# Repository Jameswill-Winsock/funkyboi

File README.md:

# funkyboi
a funky chonky handheld gba clone

he's a work in progress, please bear with him

## What is this?
like you read, a gba clone. its meant to be as small in form factor as possible, and currently i've nearly achieved this. 
it borrows from the solderparty stamp xl in form of the schematic, but pcb was remade because it wouldn't open for me for some reason. some differences between those and this are:
- lack of castelled edge based breakout (swapped to normal through holes)
- no proper power plane or signal plane (i have no idea how those work, i only know ground copper pour)
- power network significantly changed to be more unified (arguably, more unstable, but throw on some 100nf capacitors and it fixes everything.)
- the obvious gamer setup

## Parts used
please refer to "BOM reference.csv". Has everything for now,

## Journal.md
included please check

## Photos

yes i know the elephant in the room is the big red cross marks
they're marked do not populate because i want to leave the headers alone until i need them and for the actual parts that'll be needed i'll hand solder what i can

## Thanks
to you for coming here

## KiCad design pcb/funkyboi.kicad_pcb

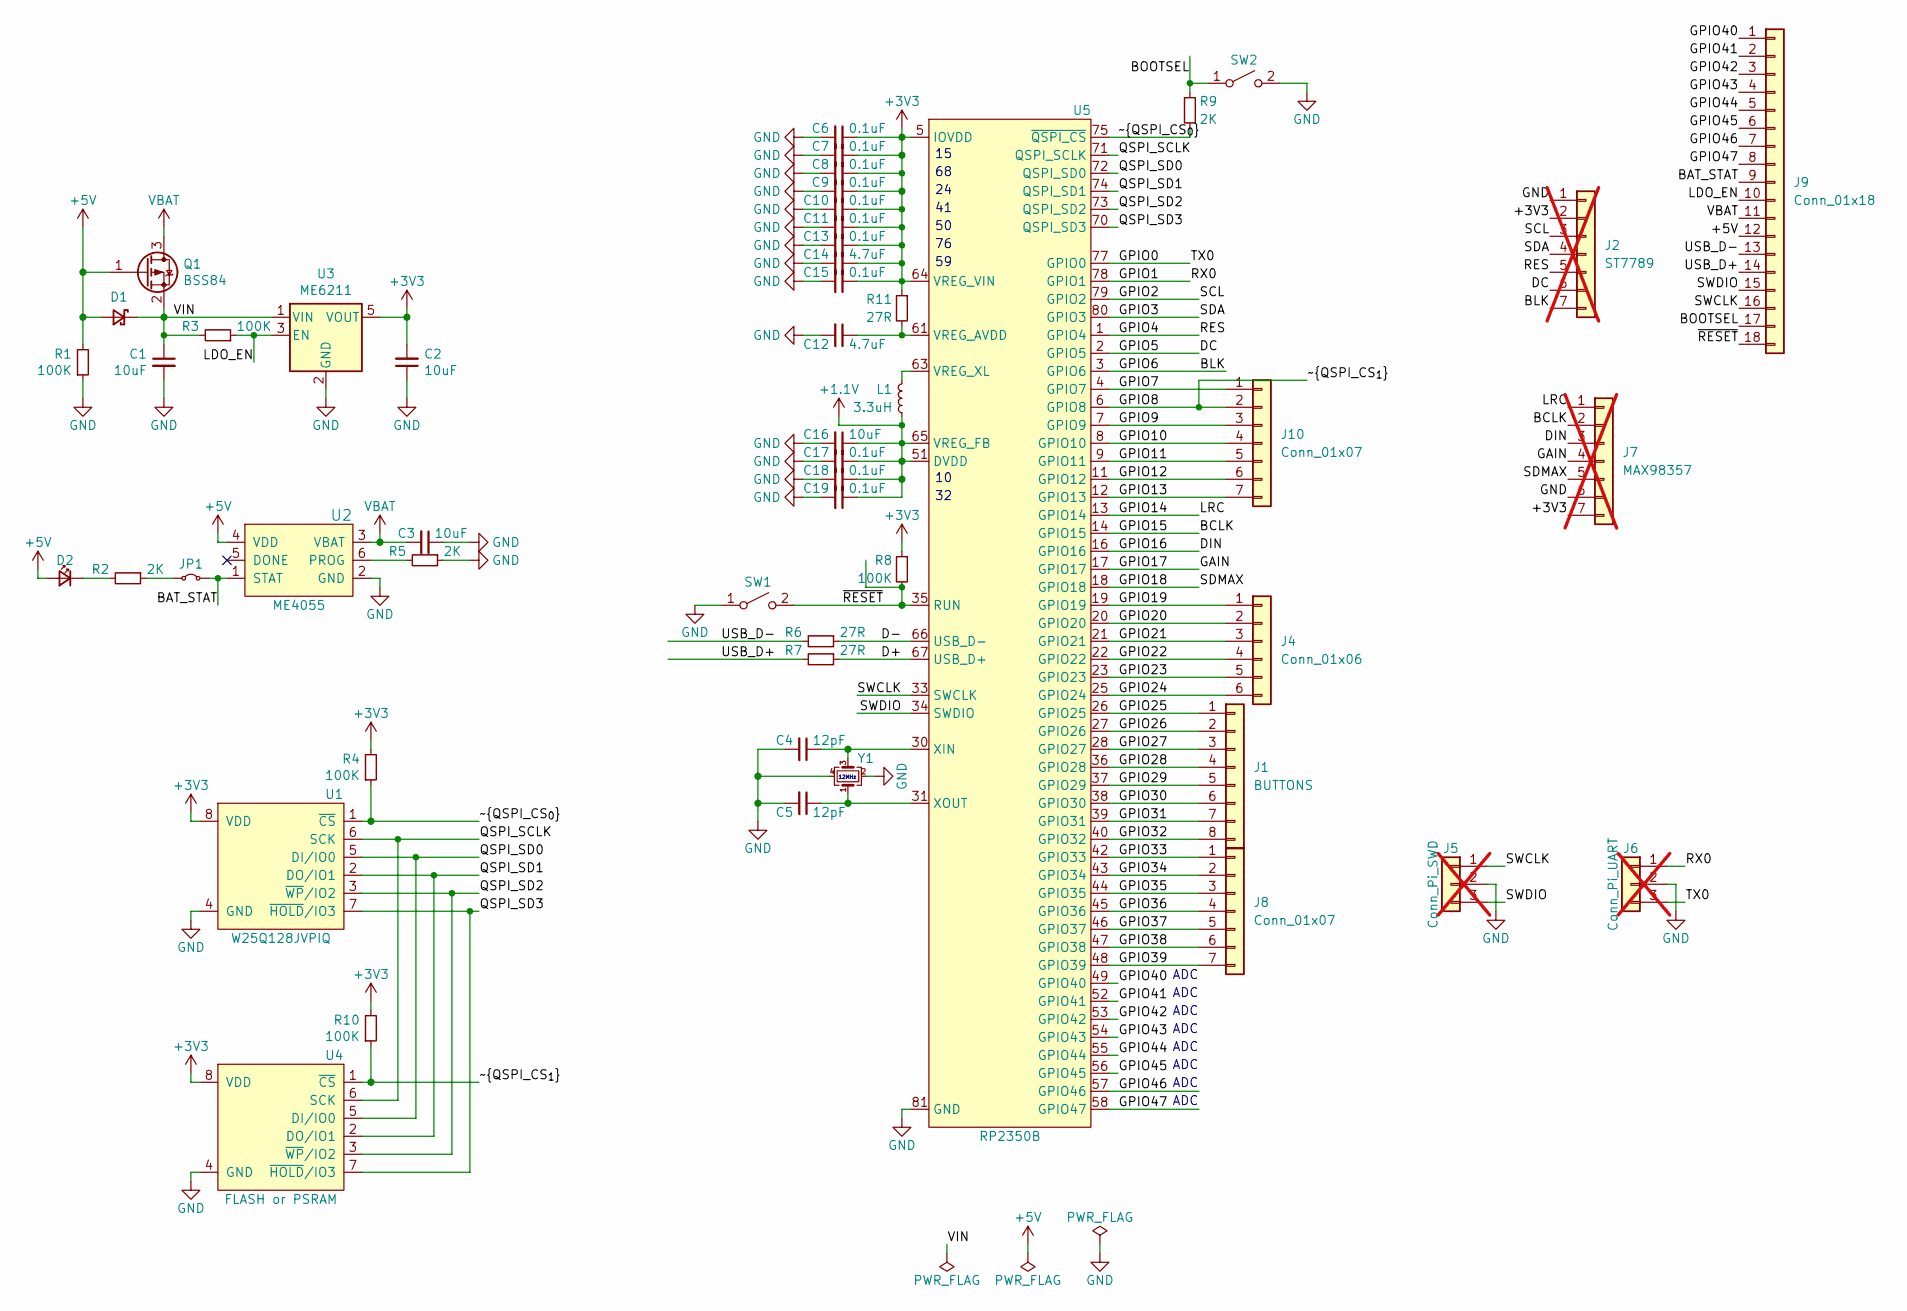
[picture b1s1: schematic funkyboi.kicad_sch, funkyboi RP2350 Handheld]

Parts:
C1, C2, C3, C16: 10uF; C_0603_1608Metric
C4, C5: 12pF; C_0603_1608Metric
C6, C7, C8, C9, C10, C11, C13, C15, C17, C18, C19: 0.1uF; C_0603_1608Metric
C12, C14: 4.7uF; C_0603_1608Metric
D1: D_Schottky_Small; D_SOD-323; LCSC C114023
D2: LED_CHR; LED_0603_1608Metric
J1: BUTTONS; PinHeader_1x08_P1.27mm_Vertical
J2: ST7789; PinSocket_1x07_P2.54mm_Vertical; not fitted
J4: Conn_01x06; PinHeader_1x06_P1.27mm_Vertical
J5: Conn_Pi_SWD; JST_SH_BM03B-SRSS-TB_1x03-1MP_P1.00mm_Vertical; LCSC C7433439; not fitted
J6: Conn_Pi_UART; JST_SH_BM03B-SRSS-TB_1x03-1MP_P1.00mm_Vertical; LCSC C7433439; not fitted
J7: MAX98357; PinHeader_1x07_P2.54mm_Vertical; not fitted
J8, J10: Conn_01x07; PinHeader_1x07_P1.27mm_Vertical
J9: Conn_01x18; PinHeader_1x18_P1.27mm_Vertical
JP1: SJ_STAT_LED; SolderJumper-2_P1.3mm_Bridged_RoundedPad1.0x1.5mm
L1: 3.3uH; L_Wuerth_MAPI-2512; LCSC C5832359
Q1: BSS84; SOT-23; LCSC C85202
R1, R3, R4, R8, R10: 100K; R_0603_1608Metric
R2, R5, R9: 2K; R_0603_1608Metric
R6, R7, R11: 27R; R_0603_1608Metric
SW1: SW_RESET; SW_SPST_B3U-1000P; LCSC C561514
SW2: SW_BOOTSEL; SW_SPST_B3U-1000P; LCSC C561514
U1: W25Q128JVPIQ; WSON-8-1EP_6x5mm_P1.27mm_EP3.4x4mm; LCSC C190862
U2: ME4055; SOT-23-6; LCSC C82121
U3: ME6211; SOT-23-5; LCSC C82942
U4: FLASH or PSRAM; SSOP-8_5.25x5.24mm_P1.27mm
U5: RP2350B; QFN-80_EP_10x10_Pitch0.4mm
Y1: CM4012M00012001; Crystal_SMD_2520-4Pin_2.5x2.0mm; LCSC C7294611

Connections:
+1.1V: C16.1, C17.1, C18.1, C19.1, L1.1, U5.10 (DVDD), U5.32 (DVDD), U5.51 (DVDD), U5.65 (VREG_FB)
+3V3: C2.2, C6.1, C7.1, C8.1, C9.1, C10.1, C11.1, C13.1, C14.1, C15.1, J2.2, J7.7, R4.2, R8.1, R10.2, R11.1, U1.8 (VDD), U3.5 (VOUT), U4.8 (VDD), U5.5 (IOVDD), U5.15 (IOVDD), U5.24 (IOVDD), U5.29 (IOVDD), U5.41 (IOVDD), U5.50 (IOVDD), U5.59 (IOVDD), U5.60 (IOVDD), U5.64 (VREG_VIN), U5.68 (IOVDD), U5.69 (IOVDD), U5.76 (IOVDD)
+5V: D1.2 (A), D2.2 (A), J9.12, Q1.1 (G), R1.2, U2.4 (VDD)
/BAT_STAT: J9.9, JP1.2 (B), U2.1 (STAT)
/BCLK: J7.2, U5.14 (GPIO15)
/BLK: J2.7, U5.3 (GPIO6)
/BOOTSEL: J9.17, R9.1, SW2.1 (A)
/D+: R7.1, U5.67 (USB_D+)
/D-: R6.1, U5.66 (USB_D-)
/DC: J2.6, U5.2 (GPIO5)
/DIN: J7.3, U5.16 (GPIO16)
/GAIN: J7.4, U5.17 (GPIO17)
/GPIO0: J6.3, U5.77 (GPIO0)
/GPIO1: J6.1, U5.78 (GPIO1)
/GPIO2: J2.3, U5.79 (GPIO2)
/GPIO3: J2.4, U5.80 (GPIO3)
/GPIO4: J2.5, U5.1 (GPIO4)
/GPIO7: J10.1, U5.4 (GPIO7)
/GPIO8: J10.2, R10.1, U4.1 (~CS), U5.6 (GPIO8)
/GPIO9: J10.3, U5.7 (GPIO9)
/GPIO10: J10.4, U5.8 (GPIO10)
/GPIO11: J10.5, U5.9 (GPIO11)
/GPIO12: J10.6, U5.11 (GPIO12)
/GPIO13: J10.7, U5.12 (GPIO13)
/GPIO14: J7.1, U5.13 (GPIO14)
/GPIO18: J7.5, U5.18 (GPIO18)
/GPIO19: J4.1, U5.19 (GPIO19)
/GPIO20: J4.2, U5.20 (GPIO20)
/GPIO21: J4.3, U5.21 (GPIO21)
/GPIO22: J4.4, U5.22 (GPIO22)
/GPIO23: J4.5, U5.23 (GPIO23)
/GPIO24: J4.6, U5.25 (GPIO24)
/GPIO25: J1.1, U5.26 (GPIO25)
/GPIO26: J1.2, U5.27 (GPIO26)
/GPIO27: J1.3, U5.28 (GPIO27)
/GPIO28: J1.4, U5.36 (GPIO28)
/GPIO29: J1.5, U5.37 (GPIO29)
/GPIO30: J1.6, U5.38 (GPIO30)
/GPIO31: J1.7, U5.39 (GPIO31)
/GPIO32: J1.8, U5.40 (GPIO32)
/GPIO33: J8.1, U5.42 (GPIO33)
/GPIO34: J8.2, U5.43 (GPIO34)
/GPIO35: J8.3, U5.44 (GPIO35)
/GPIO36: J8.4, U5.45 (GPIO36)
/GPIO37: J8.5, U5.46 (GPIO37)
/GPIO38: J8.6, U5.47 (GPIO38)
/GPIO39: J8.7, U5.48 (GPIO39)
/GPIO40: J9.1, U5.49 (GPIO40)
/GPIO41: J9.2, U5.52 (GPIO41)
/GPIO42: J9.3, U5.53 (GPIO42)
/GPIO43: J9.4, U5.54 (GPIO43)
/GPIO44: J9.5, U5.55 (GPIO44)
/GPIO45: J9.6, U5.56 (GPIO45)
/GPIO46: J9.7, U5.57 (GPIO46)
/GPIO47: J9.8, U5.58 (GPIO47)
/LDO_EN: J9.10, R3.1, U3.3 (EN)
/QSPI_SCLK: U1.6 (SCK), U4.6 (SCK), U5.71 (QSPI_SCLK)
/QSPI_SD0: U1.5 (DI/IO0), U4.5 (DI/IO0), U5.72 (QSPI_SD0)
/QSPI_SD1: U1.2 (DO/IO1), U4.2 (DO/IO1), U5.74 (QSPI_SD1)
/QSPI_SD2: U1.3 (~WP/IO2), U4.3 (~WP/IO2), U5.73 (QSPI_SD2)
/QSPI_SD3: U1.7 (~HOLD/IO3), U4.7 (~HOLD/IO3), U5.70 (QSPI_SD3)
/SWCLK: J5.1, J9.16, U5.33 (SWCLK)
/SWDIO: J5.3, J9.15, U5.34 (SWDIO)
/USB_D+: J9.14, R7.2
/USB_D-: J9.13, R6.2
/VIN: C1.1, D1.1 (K), Q1.2 (S), R3.2, U3.1 (VIN)
/~QSPI_CS_{0}: R4.1, R9.2, U1.1 (~CS), U5.75 (~QSPI_CS)
/~RESET: J9.18, R8.2, SW1.2 (B), U5.35 (RUN)
GND: C1.2, C2.1, C3.1, C4.2, C5.2, C6.2, C7.2, C8.2, C9.2, C10.2, C11.2, C12.2, C13.2, C14.2, C15.2, C16.2, C17.2, C18.2, C19.2, J2.1, J5.2, J6.2, J7.6, R1.1, R5.1, SW1.1 (A), SW2.2 (B), U1.4 (GND), U1.9 (GND), U2.2 (GND), U3.2 (GND), U4.4 (GND), U4.9 (GND), U5.62 (GND), U5.81 (GND), Y1.2, Y1.4
unnamed: D2.1 (K), R2.2
unnamed: JP1.1 (A), R2.1
unnamed: R5.2, U2.6 (PROG)
unnamed: C12.1, R11.2, U5.61 (VREG_AVDD)
unnamed: L1.2, U5.63 (VREG_XL)
unnamed: C4.1, U5.30 (XIN), Y1.3
unnamed: C5.1, U5.31 (XOUT), Y1.1
VBAT: C3.2, J9.11, Q1.3 (D), U2.3 (VBAT)

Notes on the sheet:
ADC
12MHz

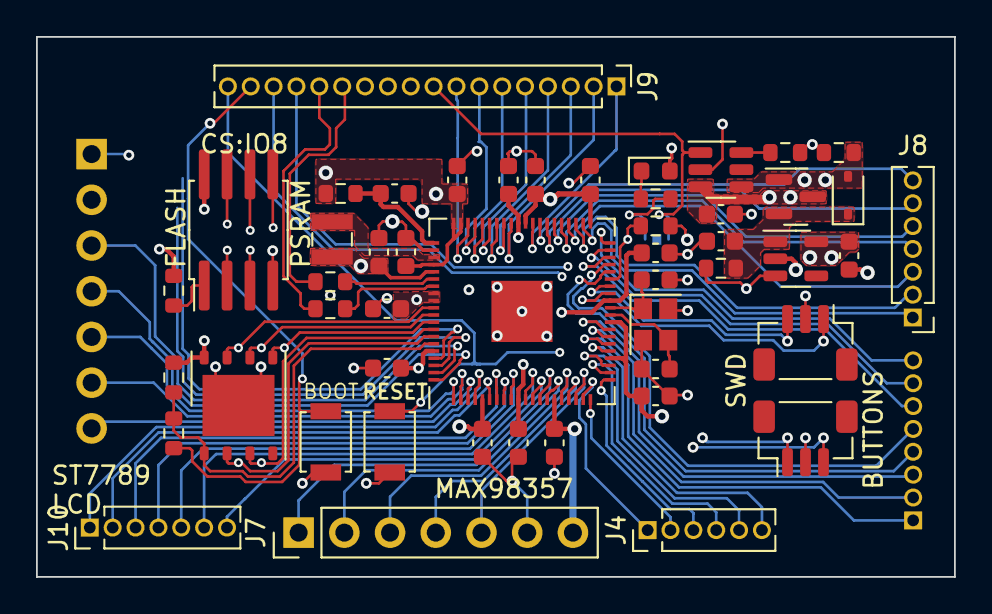
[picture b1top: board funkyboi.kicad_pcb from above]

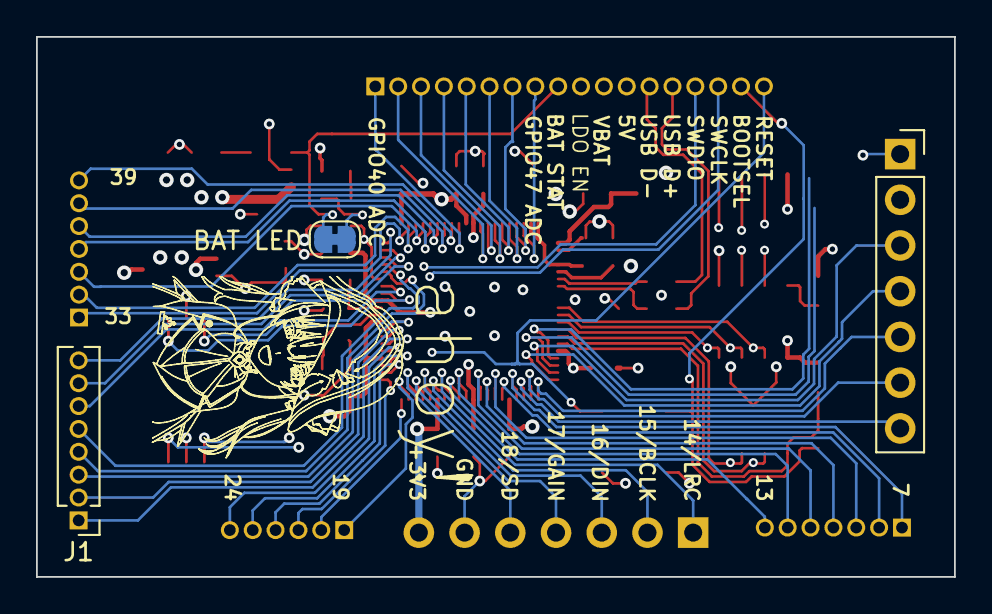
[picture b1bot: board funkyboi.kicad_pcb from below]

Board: 4 copper layers, 51.0 x 30.0 mm, 52 parts (3 on the bottom side), 77 nets.

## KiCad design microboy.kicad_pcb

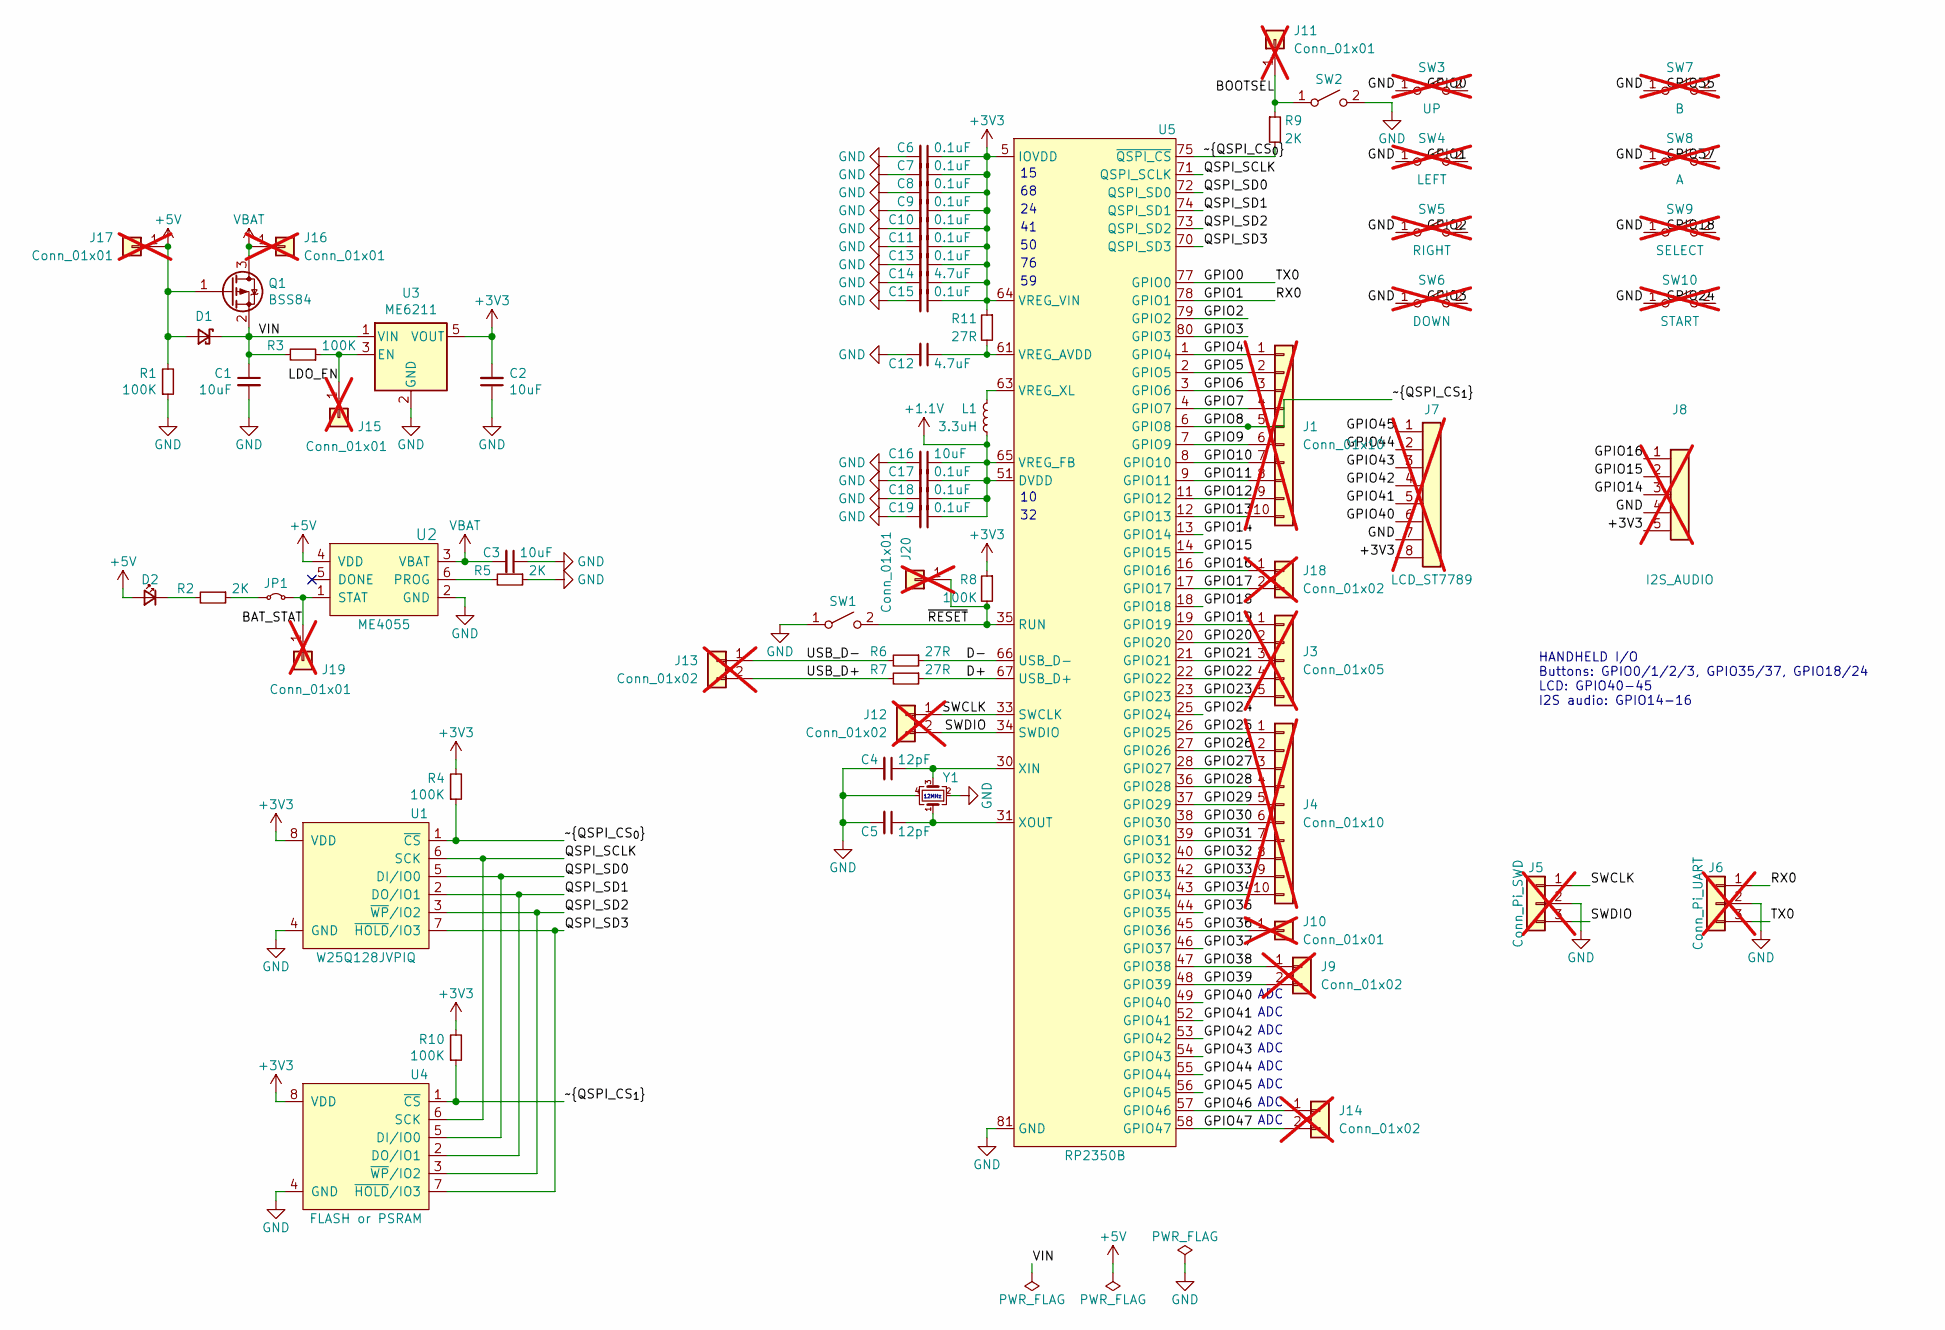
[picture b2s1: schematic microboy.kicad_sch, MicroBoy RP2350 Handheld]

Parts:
C1, C2, C3, C16: 10uF; C_0603_1608Metric
C4, C5: 12pF; C_0603_1608Metric
C6, C7, C8, C9, C10, C11, C13, C15, C17, C18, C19: 0.1uF; C_0603_1608Metric
C12, C14: 4.7uF; C_0603_1608Metric
D1: D_Schottky_Small; D_SOD-323; LCSC C114023
D2: LED_CHR; LED_0603_1608Metric
J1, J4: Conn_01x10; PinHeader_1x10_P1.27mm_Vertical; not fitted
J3: Conn_01x05; PinHeader_1x05_P1.27mm_Vertical; not fitted
J5: Conn_Pi_SWD; JST_SH_BM03B-SRSS-TB_1x03-1MP_P1.00mm_Vertical; LCSC C7433439; not fitted
J6: Conn_Pi_UART; JST_SH_BM03B-SRSS-TB_1x03-1MP_P1.00mm_Vertical; LCSC C7433439; not fitted
J7: LCD_ST7789; PinHeader_1x08_P2.54mm_Vertical; not fitted
J8: I2S_AUDIO; PinHeader_1x05_P2.54mm_Vertical; not fitted
J9, J12, J13, J14, J18: Conn_01x02; PinHeader_1x02_P1.27mm_Vertical; not fitted
J10, J11, J15, J16, J17, J19, J20: Conn_01x01; PinHeader_1x01_P1.27mm_Vertical; not fitted
JP1: SJ_STAT_LED; SolderJumper-2_P1.3mm_Bridged_RoundedPad1.0x1.5mm
L1: 3.3uH; L_Wuerth_MAPI-2512; LCSC C5832359
Q1: BSS84; SOT-23; LCSC C85202
R1, R3, R4, R8, R10: 100K; R_0603_1608Metric
R2, R5, R9: 2K; R_0603_1608Metric
R6, R7, R11: 27R; R_0603_1608Metric
SW1: SW_RESET; SW_SPST_B3U-1000P; LCSC C561514
SW2: SW_BOOTSEL; SW_SPST_B3U-1000P; LCSC C561514
SW3: UP; SW_SPST_B3U-1000P; not fitted
SW4: LEFT; SW_SPST_B3U-1000P; not fitted
SW5: RIGHT; SW_SPST_B3U-1000P; not fitted
SW6: DOWN; SW_SPST_B3U-1000P; not fitted
SW7: B; SW_SPST_B3U-1000P; not fitted
SW8: A; SW_SPST_B3U-1000P; not fitted
SW9: SELECT; SW_SPST_B3U-1000P; not fitted
SW10: START; SW_SPST_B3U-1000P; not fitted
U1: W25Q128JVPIQ; WSON-8-1EP_6x5mm_P1.27mm_EP3.4x4mm; LCSC C190862
U2: ME4055; SOT-23-6; LCSC C82121
U3: ME6211; SOT-23-5; LCSC C82942
U4: FLASH or PSRAM; SSOP-8_5.25x5.24mm_P1.27mm
U5: RP2350B; QFN-80_EP_10x10_Pitch0.4mm
Y1: CM4012M00012001; Crystal_SMD_2520-4Pin_2.5x2.0mm; LCSC C7294611

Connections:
+1.1V: C16.1, C17.1, C18.1, C19.1, L1.1, U5.10 (DVDD), U5.32 (DVDD), U5.51 (DVDD), U5.65 (VREG_FB)
+3V3: C2.2, C6.1, C7.1, C8.1, C9.1, C10.1, C11.1, C13.1, C14.1, C15.1, J7.8, J8.5, R4.2, R8.1, R10.2, R11.1, U1.8 (VDD), U3.5 (VOUT), U4.8 (VDD), U5.5 (IOVDD), U5.15 (IOVDD), U5.24 (IOVDD), U5.29 (IOVDD), U5.41 (IOVDD), U5.50 (IOVDD), U5.59 (IOVDD), U5.60 (IOVDD), U5.64 (VREG_VIN), U5.68 (IOVDD), U5.69 (IOVDD), U5.76 (IOVDD)
+5V: D1.2 (A), D2.2 (A), J17.1 (Pin_1_1), Q1.1 (G), R1.2, U2.4 (VDD)
/BAT_STAT: J19.1 (Pin_1_1), JP1.2 (B), U2.1 (STAT)
/BOOTSEL: J11.1 (Pin_1_1), R9.1, SW2.1 (A)
/D+: R7.1, U5.67 (USB_D+)
/D-: R6.1, U5.66 (USB_D-)
/GPIO0: J6.3, SW3.2 (B), U5.77 (GPIO0)
/GPIO1: J6.1, SW4.2 (B), U5.78 (GPIO1)
/GPIO2: SW5.2 (B), U5.79 (GPIO2)
/GPIO3: SW6.2 (B), U5.80 (GPIO3)
/GPIO4: J1.1, U5.1 (GPIO4)
/GPIO5: J1.2, U5.2 (GPIO5)
/GPIO6: J1.3, U5.3 (GPIO6)
/GPIO7: J1.4, U5.4 (GPIO7)
/GPIO8: J1.5, R10.1, U4.1 (~CS), U5.6 (GPIO8)
/GPIO9: J1.6, U5.7 (GPIO9)
/GPIO10: J1.7, U5.8 (GPIO10)
/GPIO11: J1.8, U5.9 (GPIO11)
/GPIO12: J1.9, U5.11 (GPIO12)
/GPIO13: J1.10, U5.12 (GPIO13)
/GPIO14: J8.3, U5.13 (GPIO14)
/GPIO15: J8.2, U5.14 (GPIO15)
/GPIO16: J8.1, J18.1, U5.16 (GPIO16)
/GPIO17: J18.2, U5.17 (GPIO17)
/GPIO18: SW9.2 (B), U5.18 (GPIO18)
/GPIO19: J3.1, U5.19 (GPIO19)
/GPIO20: J3.2, U5.20 (GPIO20)
/GPIO21: J3.3, U5.21 (GPIO21)
/GPIO22: J3.4, U5.22 (GPIO22)
/GPIO23: J3.5, U5.23 (GPIO23)
/GPIO24: SW10.2 (B), U5.25 (GPIO24)
/GPIO25: J4.1, U5.26 (GPIO25)
/GPIO26: J4.2, U5.27 (GPIO26)
/GPIO27: J4.3, U5.28 (GPIO27)
/GPIO28: J4.4, U5.36 (GPIO28)
/GPIO29: J4.5, U5.37 (GPIO29)
/GPIO30: J4.6, U5.38 (GPIO30)
/GPIO31: J4.7, U5.39 (GPIO31)
/GPIO32: J4.8, U5.40 (GPIO32)
/GPIO33: J4.9, U5.42 (GPIO33)
/GPIO34: J4.10, U5.43 (GPIO34)
/GPIO35: SW7.2 (B), U5.44 (GPIO35)
/GPIO36: J10.1 (Pin_1_1), U5.45 (GPIO36)
/GPIO37: SW8.2 (B), U5.46 (GPIO37)
/GPIO38: J9.1, U5.47 (GPIO38)
/GPIO39: J9.2, U5.48 (GPIO39)
/GPIO40: J7.6, U5.49 (GPIO40)
/GPIO41: J7.5, U5.52 (GPIO41)
/GPIO42: J7.4, U5.53 (GPIO42)
/GPIO43: J7.3, U5.54 (GPIO43)
/GPIO44: J7.2, U5.55 (GPIO44)
/GPIO45: J7.1, U5.56 (GPIO45)
/GPIO46: J14.1, U5.57 (GPIO46)
/GPIO47: J14.2, U5.58 (GPIO47)
/LDO_EN: J15.1 (Pin_1_1), R3.1, U3.3 (EN)
/QSPI_SCLK: U1.6 (SCK), U4.6 (SCK), U5.71 (QSPI_SCLK)
/QSPI_SD0: U1.5 (DI/IO0), U4.5 (DI/IO0), U5.72 (QSPI_SD0)
/QSPI_SD1: U1.2 (DO/IO1), U4.2 (DO/IO1), U5.74 (QSPI_SD1)
/QSPI_SD2: U1.3 (~WP/IO2), U4.3 (~WP/IO2), U5.73 (QSPI_SD2)
/QSPI_SD3: U1.7 (~HOLD/IO3), U4.7 (~HOLD/IO3), U5.70 (QSPI_SD3)
/SWCLK: J5.1, J12.1, U5.33 (SWCLK)
/SWDIO: J5.3, J12.2, U5.34 (SWDIO)
/USB_D+: J13.2, R7.2
/USB_D-: J13.1, R6.2
/VIN: C1.1, D1.1 (K), Q1.2 (S), R3.2, U3.1 (VIN)
/~QSPI_CS_{0}: R4.1, R9.2, U1.1 (~CS), U5.75 (~QSPI_CS)
/~RESET: J20.1 (Pin_1_1), R8.2, SW1.2 (B), U5.35 (RUN)
GND: C1.2, C2.1, C3.1, C4.2, C5.2, C6.2, C7.2, C8.2, C9.2, C10.2, C11.2, C12.2, C13.2, C14.2, C15.2, C16.2, C17.2, C18.2, C19.2, J5.2, J6.2, J7.7, J8.4, R1.1, R5.1, SW1.1 (A), SW2.2 (B), SW3.1 (A), SW4.1 (A), SW5.1 (A), SW6.1 (A), SW7.1 (A), SW8.1 (A), SW9.1 (A), SW10.1 (A), U1.4 (GND), U1.9 (GND), U2.2 (GND), U3.2 (GND), U4.4 (GND), U4.9 (GND), U5.62 (GND), U5.81 (GND), Y1.2, Y1.4
unnamed: D2.1 (K), R2.2
unnamed: JP1.1 (A), R2.1
unnamed: R5.2, U2.6 (PROG)
unnamed: C12.1, R11.2, U5.61 (VREG_AVDD)
unnamed: L1.2, U5.63 (VREG_XL)
unnamed: C4.1, U5.30 (XIN), Y1.3
unnamed: C5.1, U5.31 (XOUT), Y1.1
VBAT: C3.2, J16.1 (Pin_1_1), Q1.3 (D), U2.3 (VBAT)

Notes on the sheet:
ADC
12MHz
HANDHELD I/O Buttons: GPIO0/1/2/3, GPIO35/37, GPIO18/24 LCD: GPIO40-45 I2S audio: GPIO14-16

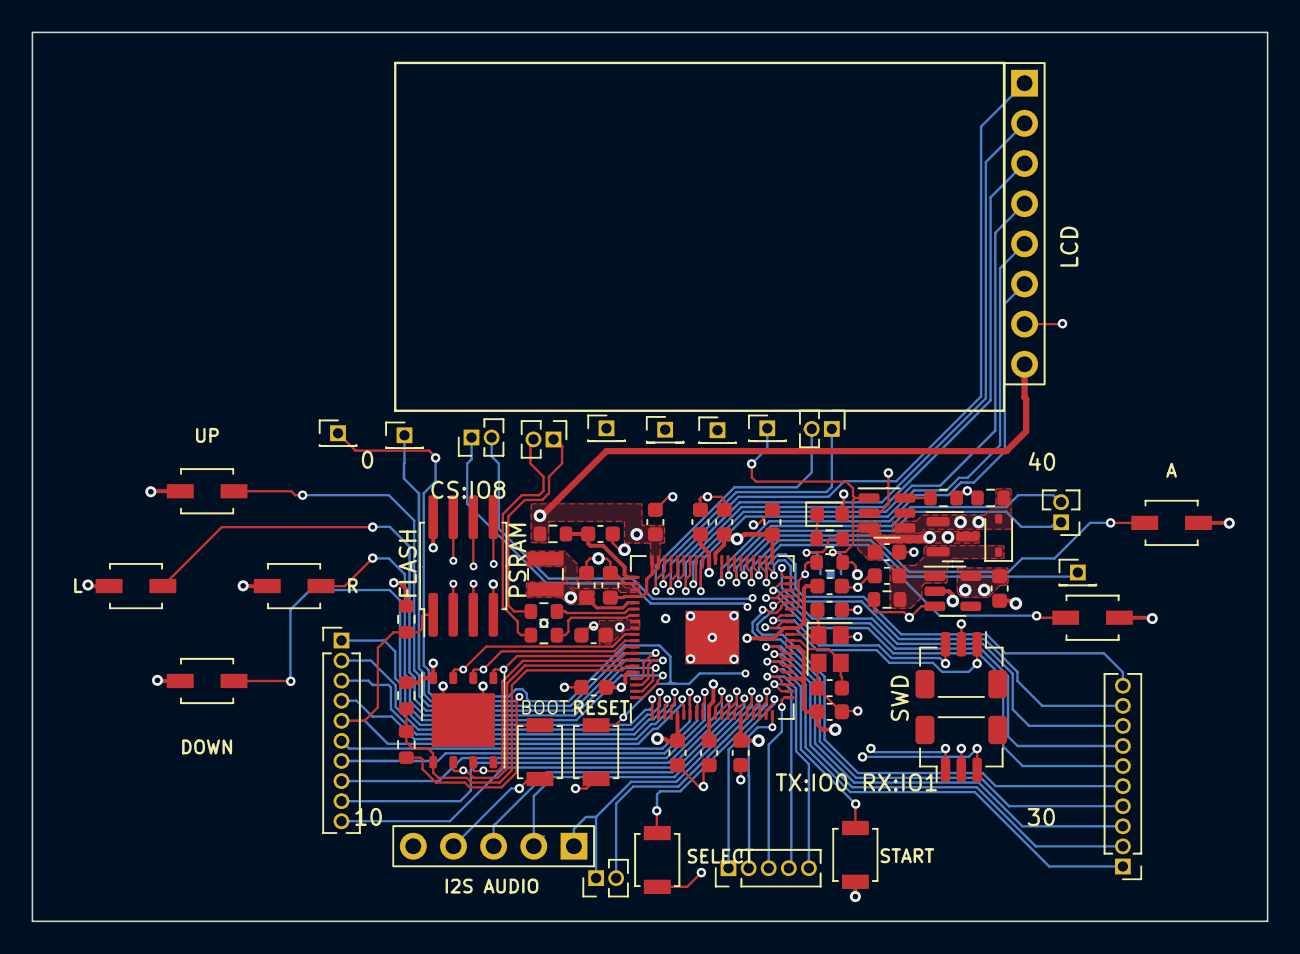
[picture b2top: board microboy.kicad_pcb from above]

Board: 4 copper layers, 78.1 x 56.2 mm, 70 parts (1 on the bottom side), 77 nets.

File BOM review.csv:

Reference,Value,Footprint,Qty,LCSC,Description
"C4,C5",12pF,Capacitor_SMD:C_0603_1608Metric,2,,
"C6,C7,C8,C9,C10,C11,C13,C15,C17,C18,C19",0.1uF,Capacitor_SMD:C_0603_1608Metric,11,,
L1,3.3uH,Inductor_SMD:L_Wuerth_MAPI-2512,1,C5832359,FTC252010S3R3MBCA
"C12,C14",4.7uF,Capacitor_SMD:C_0603_1608Metric,2,,
"C1,C2,C3,C16",10uF,Capacitor_SMD:C_0603_1608Metric,4,,
"R6,R7,R11",27R,Resistor_SMD:R_0603_1608Metric,3,,
"R2,R5,R9",2K,Resistor_SMD:R_0603_1608Metric,3,,
"R1,R3,R4,R8,R10",100K,Resistor_SMD:R_0603_1608Metric,5,,
SW8,A,Button_Switch_SMD:SW_SPST_B3U-1000P,1,,
SW7,B,Button_Switch_SMD:SW_SPST_B3U-1000P,1,,
Q1,BSS84,Package_TO_SOT_SMD:SOT-23,1,C85202,
Y1,CM4012M00012001,Crystal:Crystal_SMD_2520-4Pin_2.5x2.0mm,1,C7294611,
"J10,J11,J15,J16,J17,J19,J20",Conn_01x01,Connector_PinHeader_1.27mm:PinHeader_1x01_P1.27mm_Vertical,7,,"Generic connector, single row, 01x01, 1.27mm, through hole vertical"
"J9,J12,J13,J14,J18",Conn_01x02,Connector_PinHeader_1.27mm:PinHeader_1x02_P1.27mm_Vertical,5,,"Generic connector, single row, 01x02, 1.27mm, through hole vertical"
J3,Conn_01x05,Connector_PinHeader_1.27mm:PinHeader_1x05_P1.27mm_Vertical,1,,"Generic connector, single row, 01x05, 1.27mm, through hole vertical"
"J1,J4",Conn_01x10,Connector_PinHeader_1.27mm:PinHeader_1x10_P1.27mm_Vertical,2,,"Generic connector, single row, 01x10, 1.27mm, through hole vertical"
J5,Conn_Pi_SWD,Connector_JST:JST_SH_BM03B-SRSS-TB_1x03-1MP_P1.00mm_Vertical,1,C7433439,
J6,Conn_Pi_UART,Connector_JST:JST_SH_BM03B-SRSS-TB_1x03-1MP_P1.00mm_Vertical,1,C7433439,
D1,D_Schottky_Small,Diode_SMD:D_SOD-323,1,C114023,B5817WS-SJ
SW6,DOWN,Button_Switch_SMD:SW_SPST_B3U-1000P,1,,
U4,FLASH or PSRAM,Package_SO:SSOP-8_5.25x5.24mm_P1.27mm,1,,
J8,I2S_AUDIO,Connector_PinHeader_2.54mm:PinHeader_1x05_P2.54mm_Vertical,1,,
J7,LCD_ST7789,Connector_PinHeader_2.54mm:PinHeader_1x08_P2.54mm_Vertical,1,,
D2,LED_CHR,LED_SMD:LED_0603_1608Metric,1,,Orange
SW4,LEFT,Button_Switch_SMD:SW_SPST_B3U-1000P,1,,
U2,ME4055,Package_TO_SOT_SMD:SOT-23-6,1,C82121,
U3,ME6211,Package_TO_SOT_SMD:SOT-23-5,1,C82942,
SW5,RIGHT,Button_Switch_SMD:SW_SPST_B3U-1000P,1,,
U5,RP2350B,Package_DFN_QFN_Extra:QFN-80_EP_10x10_Pitch0.4mm,1,,
SW9,SELECT,Button_Switch_SMD:SW_SPST_B3U-1000P,1,,
SW10,START,Button_Switch_SMD:SW_SPST_B3U-1000P,1,,
SW2,SW_BOOTSEL,Button_Switch_SMD:SW_SPST_B3U-1000P,1,C561514,TS-3025-A-A-B
SW1,SW_RESET,Button_Switch_SMD:SW_SPST_B3U-1000P,1,C561514,TS-3025-A-A-B
SW3,UP,Button_Switch_SMD:SW_SPST_B3U-1000P,1,,
U1,W25Q128JVPIQ,Package_SON:WSON-8-1EP_6x5mm_P1.27mm_EP3.4x4mm,1,C190862,
LCD1,Waveshare_1.47in_172x320_ST7789V3,,1,,External Waveshare LCD module from supplied link; connects to existing J7 LCD_ST7789
AMP1,MAX98357A_I2S_Audio_Module,,1,,External I2S mono Class-D amplifier module; connects to existing J8 I2S_AUDIO
SPK1,4R_3W_Speaker,,1,,External 4 ohm 2-3W speaker for MAX98357A OUT+/OUT-
USB1,USB-C_5V_Power_Breakout,,1,,OPTION A: external USB-C 5V power breakout; connect VBUS to existing +5V input and GND to GND
J21,USB_C_Receptacle_USB2.0_16P,Connector_USB:USB_C_Receptacle_HRO_TYPE-C-31-M-12,1,C165948,OPTION B: raw on-board USB-C receptacle; use instead of USB1
"R12,R13",5.1K,Resistor_SMD:R_0603_1608Metric,2,C23186,USB-C CC1/CC2 pull-down resistors; required only with raw J21 option
D3,USBLC6-2SC6,Package_TO_SOT_SMD:SOT-23-6,1,C7519,USB D+/D- ESD protection; use with raw USB-C data connection
J22,BATTERY_1S,Connector_JST:JST_PH_B2B-PH-K_1x02_P2.00mm_Vertical,1,C131337,JST-PH 2.0mm 2-pin connector for 1S LiPo or protected 18650 supply
BAT1,1S_LiPo_3.7V,,1,,OPTION A battery: protected 1S LiPo pack; capacity/size to suit enclosure
BT1,18650_Holder_1S,,1,,OPTION B battery: single 18650 holder
BMS1,1S_LiIon_Protection_BMS,,1,,18650/cell only; protection-only BMS because existing ME4055 already handles charging
SW11,POWER_ON_OFF,Button_Switch_SMD:SW_SPDT_CK_JS102011SAQN,1,,SPDT slide power switch; can use existing LDO_EN/VIN/GND arrangement without changing core circuitry
